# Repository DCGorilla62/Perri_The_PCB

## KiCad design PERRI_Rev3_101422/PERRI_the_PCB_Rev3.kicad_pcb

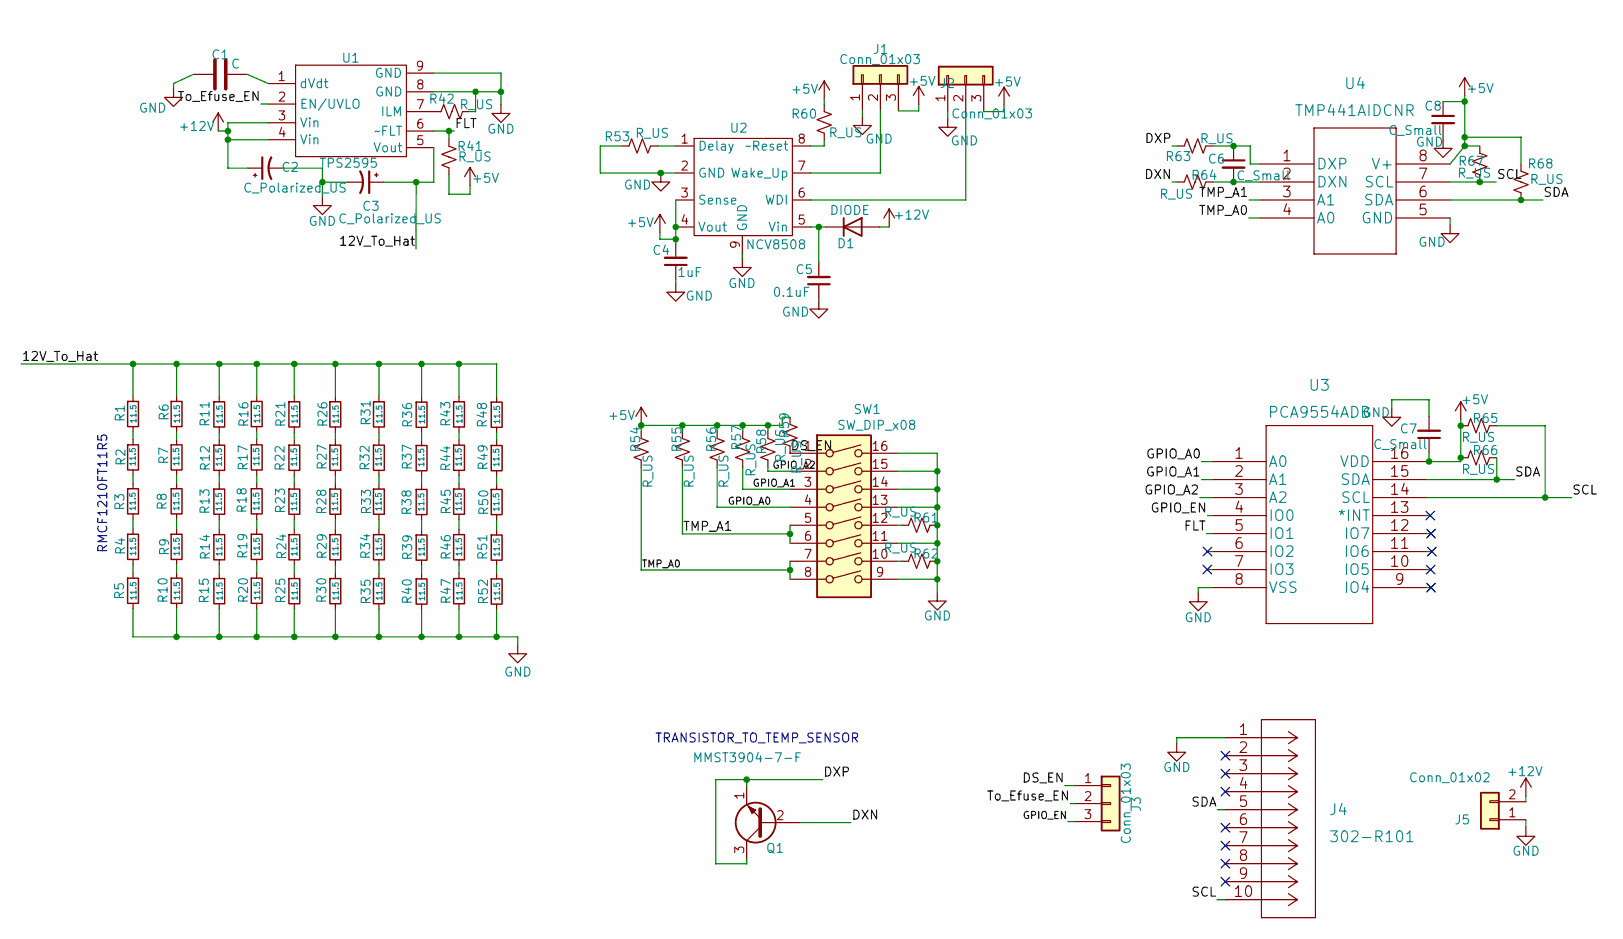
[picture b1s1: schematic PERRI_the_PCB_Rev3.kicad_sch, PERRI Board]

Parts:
C1: C; C_0805_2012Metric
C2, C3: C_Polarized_US; C_1206_3216Metric
C4: 1uF; C_1206_3216Metric
C5: 0.1uF; C_1206_3216Metric
C6, C7, C8: C_Small; C_0805_2012Metric
D1: DIODE; D_DO-41_SOD81_P5.08mm_Vertical_AnodeUp
J1, J2, J3: Conn_01x03; PinHeader_1x03_P2.54mm_Vertical
J4: 302-R101
J5: Conn_01x02; 1757242
Q1: MMST3904-7-F
R1, R2, R3, R4, R5, R6, R7, R8, R9, R10, R11, R12, R13, R14, R15, R16, R17, R18, R19, R20, R21, R22, R23, R24, R25, R26, R27, R28, R29, R30, R31, R32, R33, R34, R35, R36, R37, R38, R39, R40, R43, R44, R45, R46, R47, R48, R49, R50, R51, R52: 11.5; R_1210_3225Metric
R41, R42, R53, R54, R55, R56, R57, R58, R59, R60, R61, R62, R63, R64, R65, R66, R67, R68: R_US; R_0805_2012Metric
SW1: SW_DIP_x08; SW_219-8LPSTRF
U1: TPS2595; TPS259525DSGR
U2: NCV8508; SOIC-8-1EP_3.9x4.9mm_P1.27mm_EP2.514x3.2mm
U3: PCA9554ADB
U4: TMP441AIDCNR

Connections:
+5V: C4.2, C7.1, C8.1, J1.3, J2.3, R41.2, R54.2, R55.2, R56.2, R57.2, R58.2, R59.2, R60.2, R65.1, R66.1, R67.1, R68.1, U2.3 (Sense), U2.4 (Vout), U3.16 (VDD), U4.8 (V+)
+12V: C2.1, D1.1 (A), J5.2, U1.3 (Vin), U1.4 (Vin)
/12V_To_Hat: C3.1, R1.1, R6.1, R11.1, R16.1, R21.1, R26.1, R31.1, R36.1, R43.1, R48.1, U1.5 (Vout)
/DS_EN: J3.1, R59.1, SW1.1
/DXN: Q1.2 (B), R64.1
/DXP: Q1.1 (E), Q1.3 (C), R63.1
/FLT: R41.1, U1.6 (~FLT), U3.5 (IO1)
/GPIO_A0: R56.1, SW1.4, U3.1 (A0)
/GPIO_A1: R57.1, SW1.3, U3.2 (A1)
/GPIO_A2: R58.1, SW1.2, U3.3 (A2)
/GPIO_EN: J3.3, U3.4 (IO0)
/SCL: J4.10, R65.2, R67.2, U3.14 (SCL), U4.7 (SCL)
/SDA: J4.5, R66.2, R68.2, U3.15 (SDA), U4.6 (SDA)
/TMP_A0: R54.1, SW1.7, SW1.8, U4.4 (A0)
/TMP_A1: R55.1, SW1.5, SW1.6, U4.3 (A1)
/To_Efuse_EN: J3.2, U1.2 (EN/UVLO)
GND: C1.2, C2.2, C3.2, C4.1, C5.1, C7.2, C8.2, J1.1, J2.1, J4.1, J5.1, R5.2, R10.2, R15.2, R20.2, R25.2, R30.2, R35.2, R40.2, R42.2, R47.2, R52.2, R53.1, R61.2, R62.2, SW1.9, SW1.11, SW1.13, SW1.14, SW1.15, SW1.16, U1.8 (GND), U1.9 (GND), U2.2 (GND), U2.9 (GND), U3.8 (VSS), U4.5 (GND)
unnamed: C1.1, U1.1 (dVdt)
unnamed: C5.2, D1.2 (K), U2.5 (Vin)
unnamed: C6.1, R63.2, U4.1 (DXP)
unnamed: C6.2, R64.2, U4.2 (DXN)
unnamed: J1.2, U2.7 (Wake_Up)
unnamed: J2.2, U2.6 (WDI)
unnamed: R1.2, R2.1
unnamed: R2.2, R3.1
unnamed: R3.2, R4.1
unnamed: R4.2, R5.1
unnamed: R6.2, R7.1
unnamed: R7.2, R8.1
unnamed: R8.2, R9.1
unnamed: R9.2, R10.1
unnamed: R11.2, R12.1
unnamed: R12.2, R13.1
unnamed: R13.2, R14.1
unnamed: R14.2, R15.1
unnamed: R16.2, R17.1
unnamed: R17.2, R18.1
unnamed: R18.2, R19.1
unnamed: R19.2, R20.1
unnamed: R21.2, R22.1
unnamed: R22.2, R23.1
unnamed: R23.2, R24.1
unnamed: R24.2, R25.1
unnamed: R26.2, R27.1
unnamed: R27.2, R28.1
unnamed: R28.2, R29.1
unnamed: R29.2, R30.1
unnamed: R31.2, R32.1
unnamed: R32.2, R33.1
unnamed: R33.2, R34.1
unnamed: R34.2, R35.1
unnamed: R36.2, R37.1
unnamed: R37.2, R38.1
unnamed: R38.2, R39.1
unnamed: R39.2, R40.1
unnamed: R42.1, U1.7 (ILM)
unnamed: R43.2, R44.1
unnamed: R44.2, R45.1
unnamed: R45.2, R46.1
unnamed: R46.2, R47.1
unnamed: R48.2, R49.1
unnamed: R49.2, R50.1
unnamed: R50.2, R51.1
unnamed: R51.2, R52.1
unnamed: R53.2, U2.1 (Delay)
unnamed: R60.1, U2.8 (~Reset)
unnamed: R61.1, SW1.12
unnamed: R62.1, SW1.10

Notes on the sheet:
TRANSISTOR_TO_TEMP_SENSOR
RMCF1210FT11R5

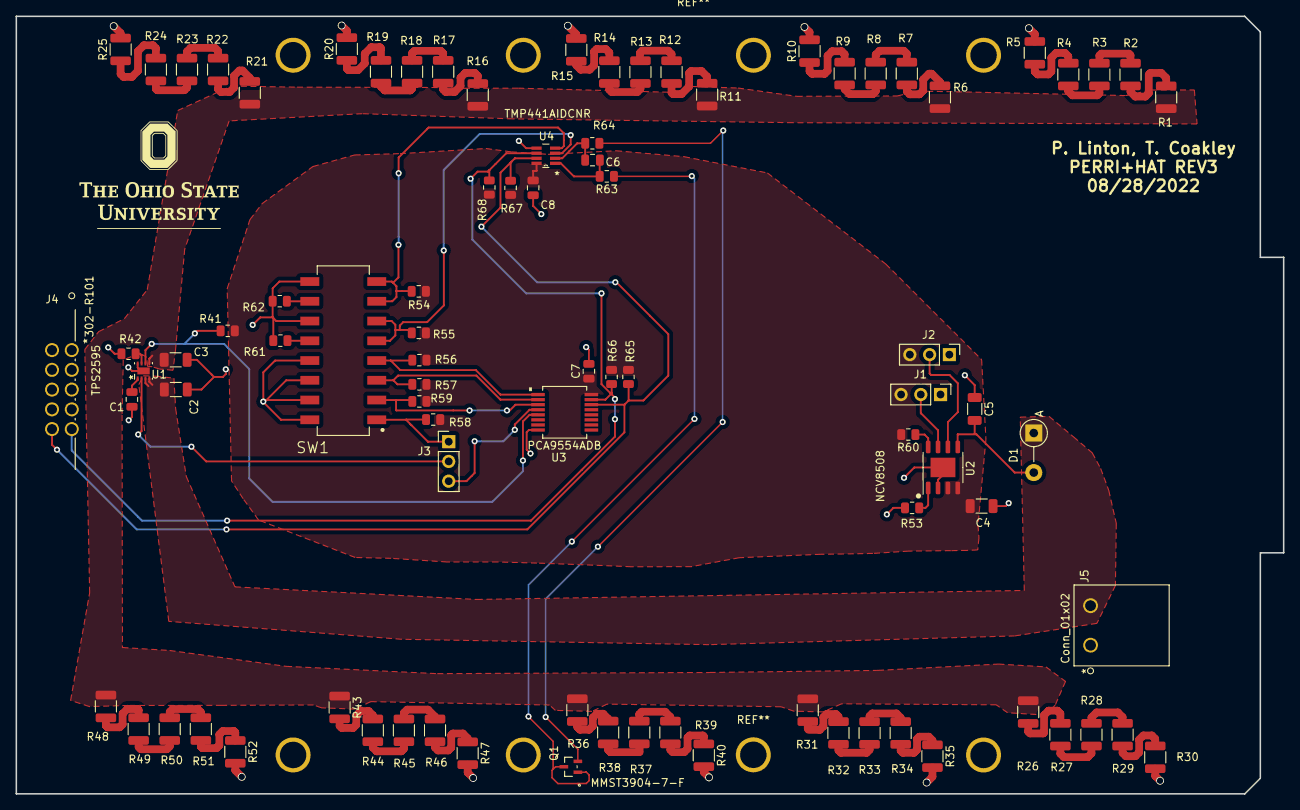
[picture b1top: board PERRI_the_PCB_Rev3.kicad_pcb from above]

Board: 2 copper layers, 163.0 x 100.0 mm, 88 parts (0 on the bottom side), 68 nets.

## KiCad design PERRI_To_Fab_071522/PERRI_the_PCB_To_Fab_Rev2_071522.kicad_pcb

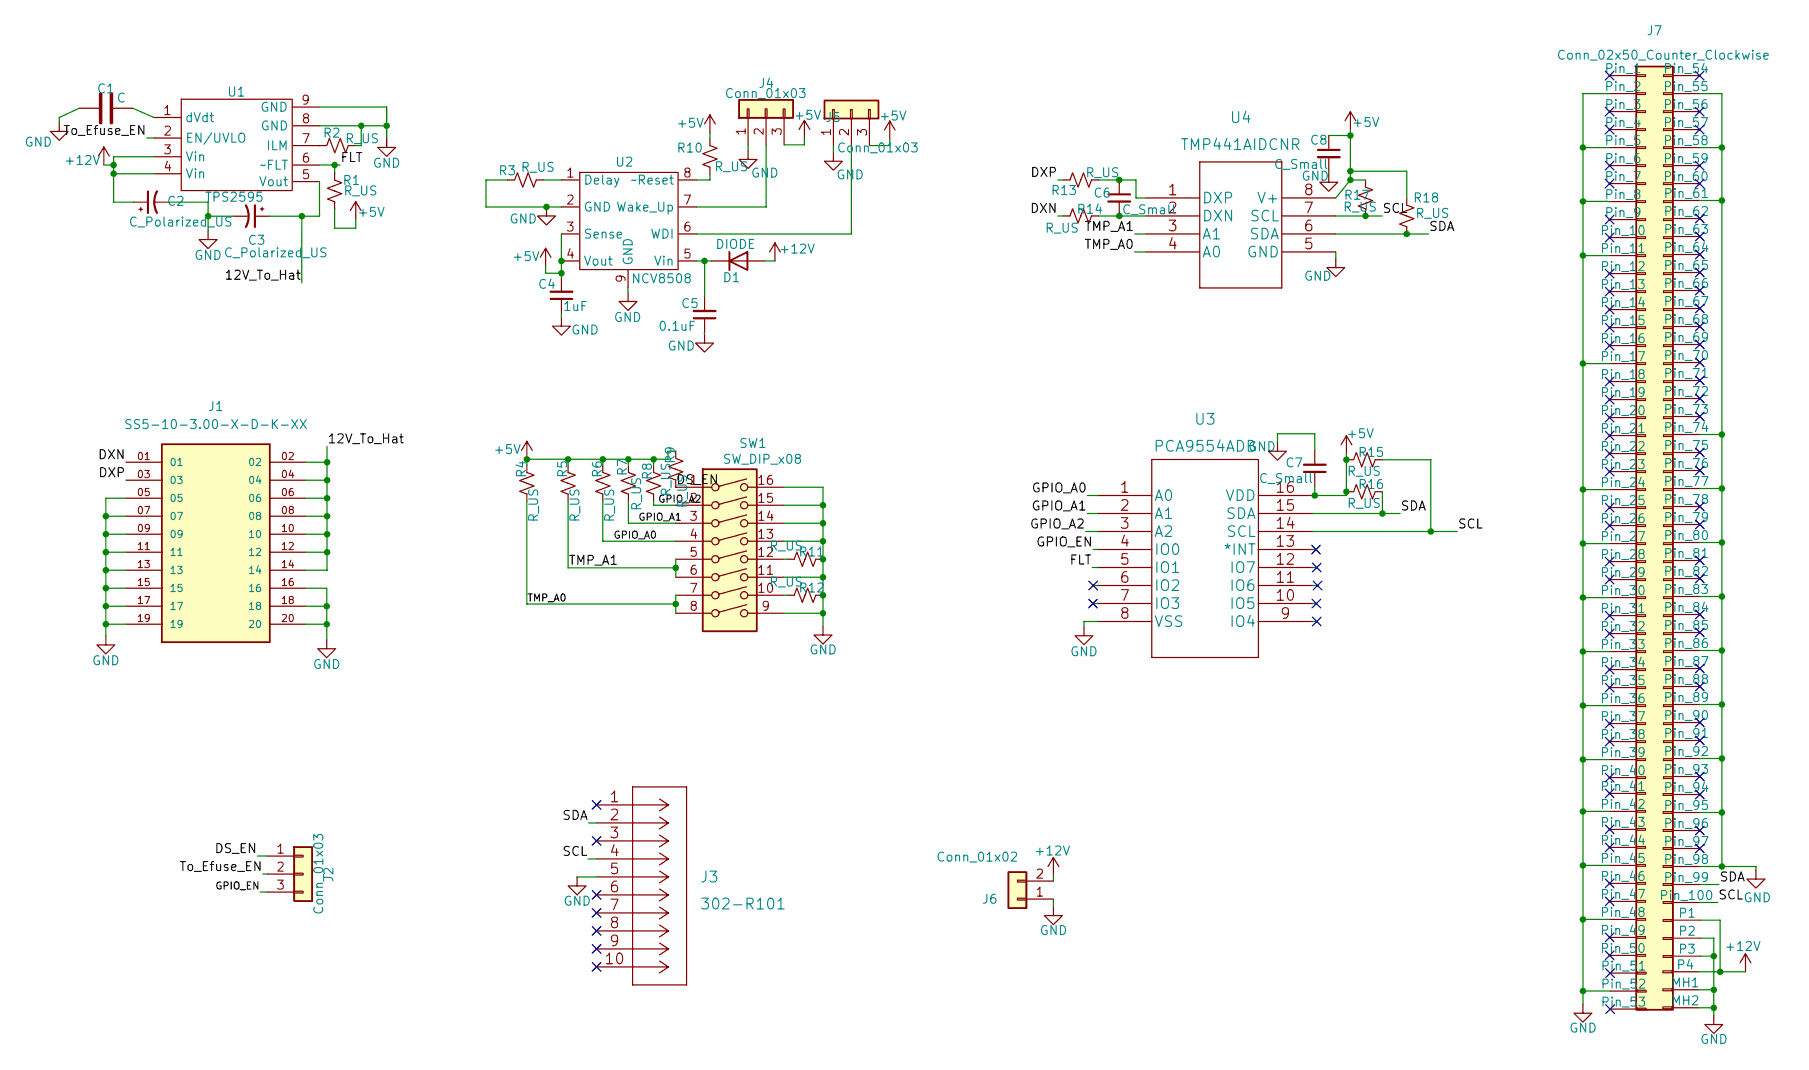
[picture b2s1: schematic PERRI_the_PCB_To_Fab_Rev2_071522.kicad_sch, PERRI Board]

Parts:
C1: C; C_0805_2012Metric
C2, C3: C_Polarized_US; C_1206_3216Metric
C4: 1uF; C_1206_3216Metric
C5: 0.1uF; C_1206_3216Metric
C6, C7, C8: C_Small; C_0805_2012Metric
D1: DIODE; D_DO-41_SOD81_P5.08mm_Vertical_AnodeUp
J1: SS5-10-3.00-X-D-K-XX; SAMTEC_SS5-10-3.00-X-D-K-XX; PARTREV F
J2, J4, J5: Conn_01x03; PinHeader_1x03_P2.54mm_Vertical
J3: 302-R101
J6: Conn_01x02; 1757242
J7: Conn_02x50_Counter_Clockwise; FX23100S05SH
R1, R2, R3, R4, R5, R6, R7, R8, R9, R10, R11, R12, R13, R14, R15, R16, R17, R18: R_US; R_0805_2012Metric
SW1: SW_DIP_x08; SW_219-8LPSTRF
U1: TPS2595; TPS259525DSGR
U2: NCV8508; SOIC-8-1EP_3.9x4.9mm_P1.27mm_EP2.514x3.2mm
U3: PCA9554ADB
U4: TMP441AIDCNR

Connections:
+5V: C4.2, C7.1, C8.1, J4.3, J5.3, R1.2, R4.2, R5.2, R6.2, R7.2, R8.2, R9.2, R10.2, R15.1, R16.1, R17.1, R18.1, U2.3 (Sense), U2.4 (Vout), U3.16 (VDD), U4.8 (V+)
+12V: C2.1, D1.1 (A), J6.2, J7.P1, J7.P4, U1.3 (Vin), U1.4 (Vin)
/12V_To_Hat: C3.1, J1.02, J1.04, J1.06, J1.08, J1.10, J1.12, J1.14, U1.5 (Vout)
/DS_EN: J2.1, R9.1, SW1.1
/DXN: J1.01, R14.1
/DXP: J1.03, R13.1
/FLT: R1.1, U1.6 (~FLT), U3.5 (IO1)
/GPIO_A0: R6.1, SW1.4, U3.1 (A0)
/GPIO_A1: R7.1, SW1.3, U3.2 (A1)
/GPIO_A2: R8.1, SW1.2, U3.3 (A2)
/GPIO_EN: J2.3, U3.4 (IO0)
/SCL: J3.4, J7.100, R15.2, R17.2, U3.14 (SCL), U4.7 (SCL)
/SDA: J3.2, J7.99, R16.2, R18.2, U3.15 (SDA), U4.6 (SDA)
/TMP_A0: R4.1, SW1.7, SW1.8, U4.4 (A0)
/TMP_A1: R5.1, SW1.5, SW1.6, U4.3 (A1)
/To_Efuse_EN: J2.2, U1.2 (EN/UVLO)
GND: C1.2, C2.2, C3.2, C4.1, C5.1, C7.2, C8.2, J1.05, J1.07, J1.09, J1.11, J1.13, J1.15, J1.16, J1.17, J1.18, J1.19, J1.20, J3.5, J4.1, J5.1, J6.1, J7.2, J7.5, J7.8, J7.11, J7.17, J7.24, J7.27, J7.30, J7.33, J7.36, J7.39, J7.42, J7.45, J7.48, J7.52, J7.55, J7.58, J7.61, J7.74, J7.77, J7.80, J7.83, J7.86, J7.89, J7.92, J7.95, J7.98, J7.MH1, J7.MH2, J7.P2, J7.P3, R2.2, R3.1, R11.2, R12.2, SW1.9, SW1.11, SW1.13, SW1.14, SW1.15, SW1.16, U1.8 (GND), U1.9 (GND), U2.2 (GND), U2.9 (GND), U3.8 (VSS), U4.5 (GND)
unnamed: C1.1, U1.1 (dVdt)
unnamed: C5.2, D1.2 (K), U2.5 (Vin)
unnamed: C6.1, R13.2, U4.1 (DXP)
unnamed: C6.2, R14.2, U4.2 (DXN)
unnamed: J4.2, U2.7 (Wake_Up)
unnamed: J5.2, U2.6 (WDI)
unnamed: R2.1, U1.7 (ILM)
unnamed: R3.2, U2.1 (Delay)
unnamed: R10.1, U2.8 (~Reset)
unnamed: R11.1, SW1.12
unnamed: R12.1, SW1.10

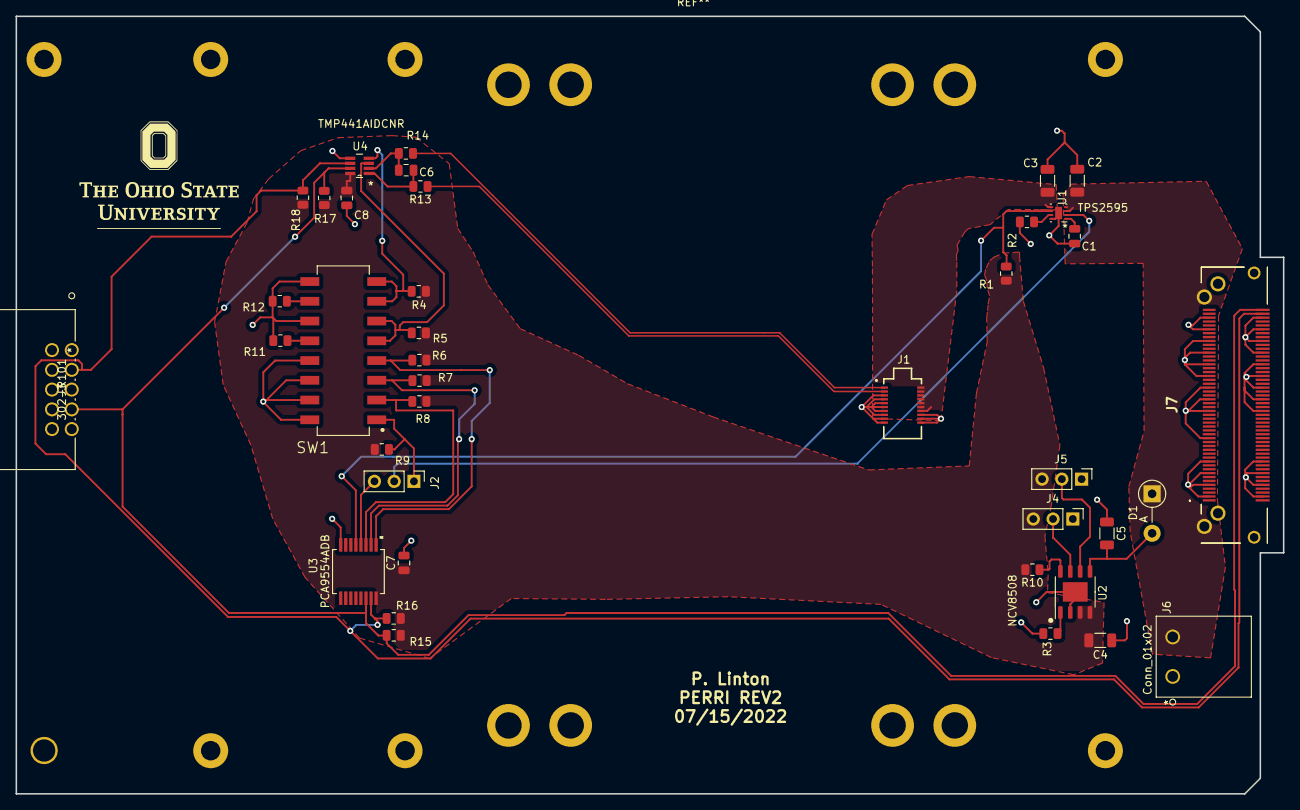
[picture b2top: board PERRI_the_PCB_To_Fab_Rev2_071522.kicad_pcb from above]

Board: 2 copper layers, 163.0 x 100.0 mm, 40 parts (0 on the bottom side), 28 nets.

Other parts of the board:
PERRI Mounting Holes: PERRI_Mounting_Holes

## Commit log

2022-07-08 Added the Perri files
2022-07-11 made changes to rev 2
2022-07-12 Fixed some alignment issues
2022-07-13 Ready for Fab
2022-07-13 improved organization kinda
2022-07-13 To fab files
2022-07-13 Changed the two 160 pin conn to one 20 pin conn
2022-07-13 changed name, had the wrong date
2022-07-15 changed 2x5 connector on PERRI
2022-08-30 PERRI rev 3
2022-10-14 New PERRI
    Fixed, hopefully, the transistor wiring
2022-10-14 Fixed transistor issue. Review completed. -Dennis H. Calderon

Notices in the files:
parts and their libraries:
Copyright 2021 Accelerated Designs. All rights reserved.
